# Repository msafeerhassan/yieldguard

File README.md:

# YieldGuard

## An automatic Milk Weight Logging System using ESP32, HX711 and Load Cell

### How it works:
1. The whole hardware sits under the milk collection Jar.
2. The milk gets collected inside the Jar - Hardware silently notices it.
3. When the milking completes, the weight becomes stable.
4. Once it stabilizes for more than 3 minutes, the milk weight gets logged and is sent over WhatsApp as a message.
5. It repeats :)

#### How to use it?

1. Go over to [JLCPCB](https://jlcpcb.com/).
2. Download the Gerber Files from this repository and upload them there and order PCB.
3. Use the links in BoM (Bill of Materials) to order other components (The 3D Case can either be 3D-Printed or pre-made case can be ordered).
4. Solder all the components on PCB and wire them properly as per the Schematic Diagram.
5. Connect ESP32 with your device and boot the Calibration Code in it.
6. Follow all the instructions mentioned in Serial Monitor to calibrate the Load Cell Specs etc.
7. Boot ESP32 with the main code given in Firmware/Main/main.ino file.
8. That's all :) Enjoy.

#### Why I built this?

I built this project to solve the real problem we faced at our farm - manual milk logging was quite difficult and unreliable. This automatic milk logging system makes the system highly reliable and efficient.

#### Screenshots:

#### Bill of Materials

| Item Name | Quantity | Link | Cost |
| :--- | :--- | :--- | :--- |
| ESP32-C3-SuperMini | 1 | https://epro.pk/product/esp32-c3-wireless-development-board-wifi-bluetooth/ | $2.53 |
| CZL-601 Aluminum Alloy 100kg Load Cell | 1 | https://www.aliexpress.com/item/1005007658937664.html | $13.00 |
| HX711 Module | 1 | https://epro.pk/product/arduino-load-cell-amplifier-hx711-hx-711-digital-scale/ | $0.60 |
| 3D Case | 1 | https://epro.pk/product/waterproof-electronic-enclosure-box-150x110x75mm-4x6x3-inch-in-pakistan/ - Can be 3D Printed also | $1.00 |
| PCB | 5 | JLCPCB | $16 |
| AliExpress Taxes | - | - | $7.80 |
| ePro.Pk Shipping Charges | - | - | $1 |
| TOTAL COST | - | - | $42 |

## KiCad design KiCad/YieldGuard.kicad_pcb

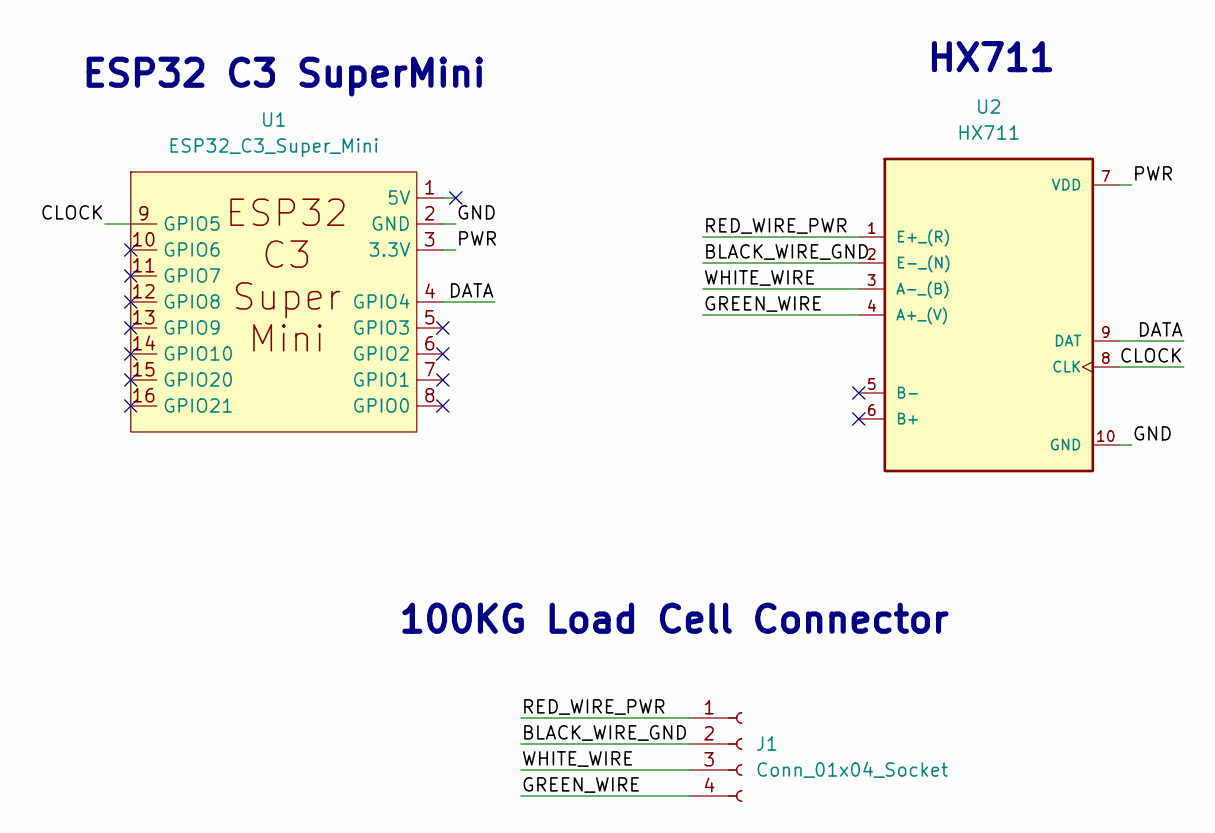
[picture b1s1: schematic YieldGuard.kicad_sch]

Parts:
J1: Conn_01x04_Socket; TerminalBlock_Phoenix_MKDS-1,5-4-5.08_1x04_P5.08mm_Horizont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
U1: ESP32_C3_Super_Mini; ESP32-C3_SuperMini
U2: HX711; HX711_module

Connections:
/BLACK_WIRE_GND: J1.2, U2.2 (E-_(N))
/CLOCK: U1.9 (GPIO5), U2.8 (CLK)
/DATA: U1.4 (GPIO4), U2.9 (DAT)
/GND: U1.2 (GND), U2.10 (GND)
/GREEN_WIRE: J1.4, U2.4 (A+_(V))
/PWR: U1.3 (3.3V), U2.7 (VDD)
/RED_WIRE_PWR: J1.1, U2.1 (E+_(R))
/WHITE_WIRE: J1.3, U2.3 (A-_(B))

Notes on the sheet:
HX711
ESP32 C3 SuperMini
100KG Load Cell Connector

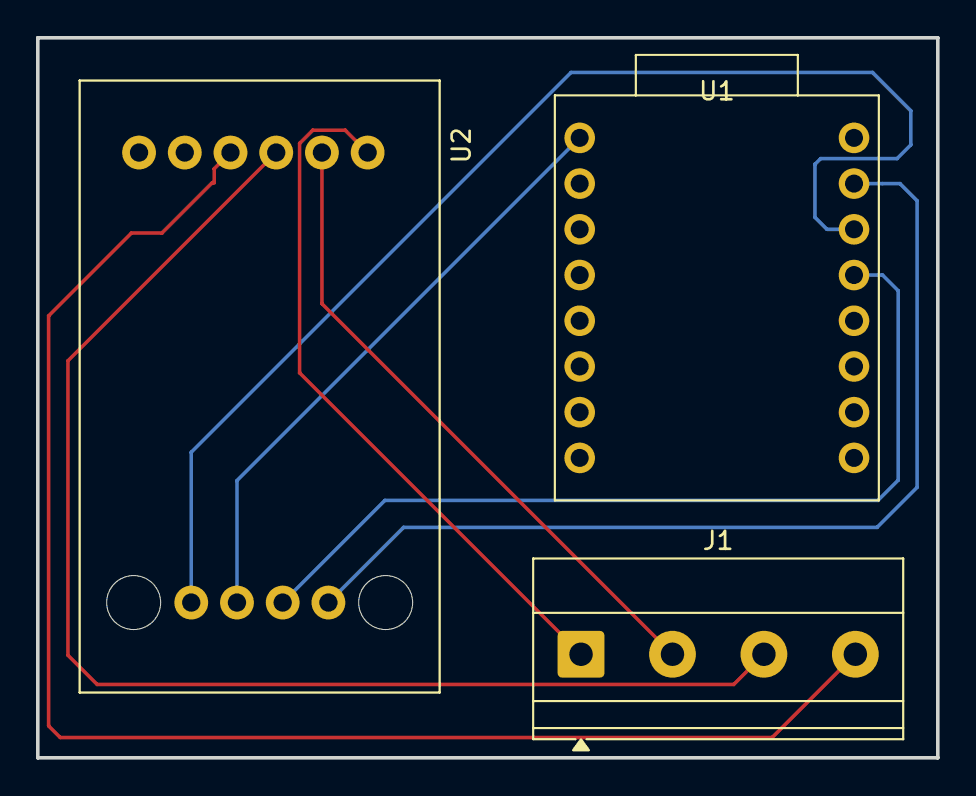
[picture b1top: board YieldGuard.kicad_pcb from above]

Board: 2 copper layers, 50.0 x 40.0 mm, 3 parts (0 on the bottom side), 8 nets.

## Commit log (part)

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2026-05-24 Adding draft BoM
2026-05-24 Add KiCad files - schematic complete
2026-05-25 added complete pcb design with gerber files
2026-05-25 rounded pcb corners - final touch to the pcb
2026-05-25 fixed the dimension of screw terminal of load cell
2026-05-25 Bit changes in PCB and Schematic and Completed BoM
2026-05-26 routed updated PCB
2026-05-31 finished BoM, PCB, 3D
2026-06-29 added firmware and improved bom and readme
2026-06-29 fixed readme
2026-06-29 added stl file
2026-06-29 kicad fixes
